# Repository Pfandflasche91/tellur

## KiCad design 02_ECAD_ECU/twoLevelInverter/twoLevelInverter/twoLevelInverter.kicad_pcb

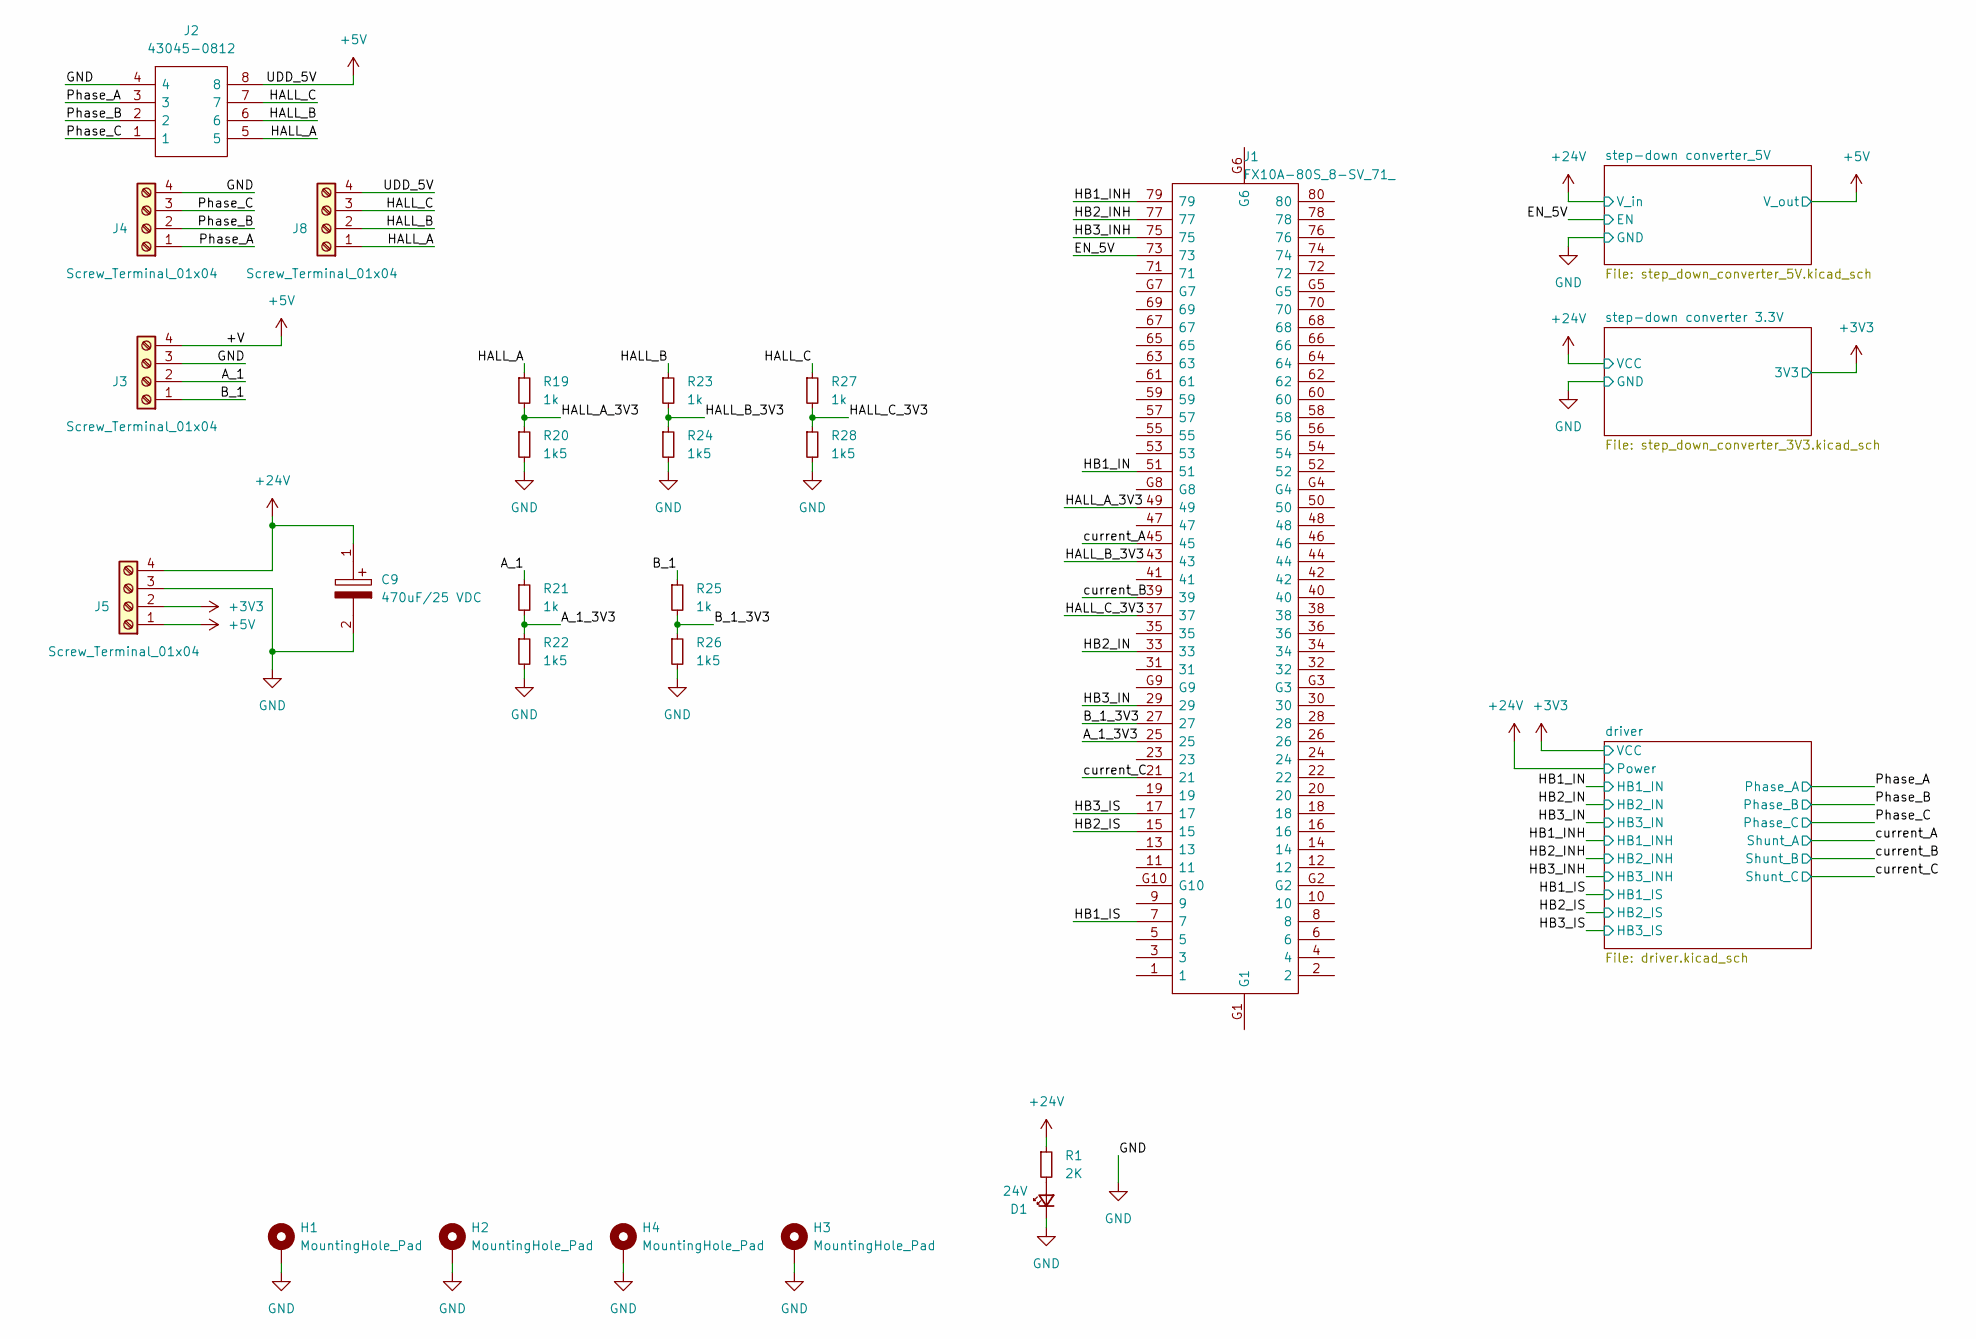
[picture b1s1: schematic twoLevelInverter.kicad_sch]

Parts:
C9: 470uF/25 VDC; CAPAE1030X1050N; Mouser Part Number 710-865080457015
D1: 24V; LED_0805_2012Metric
H1, H2, H3, H4: MountingHole_Pad; MountingHole_5.3mm_M5_Pad_Via
J1: FX10A-80S_8-SV_71_; FX10A80S8SV71; Mouser Part Number 798-FX10A80S8SV71
J2: 43045-0812; 43045-08YY_121314; Mouser Part Number 538-43045-0812
J3, J4, J5, J8: Screw_Terminal_01x04; screwconnector_4_wuerth
R1: 2K; R_1206_3216Metric
R19, R21, R23, R25, R27: 1k; R_1206_3216Metric
R20, R22, R24, R26, R28: 1k5; R_1206_3216Metric

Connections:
+3V3: J5.2; also elsewhere on the board
+5V: J2.8, J3.4, J5.1, J8.4; also elsewhere on the board
+24V: C9.1, J5.4, R1.1; also elsewhere on the board
/A_1: J3.2, R21.1
/A_1_3V3: J1.25, R21.2, R22.1
/B_1: J3.1, R25.1
/B_1_3V3: J1.27, R25.2, R26.1
/EN_5V: J1.73; also elsewhere on the board
/HALL_A: J2.5, J8.1, R19.1
/HALL_A_3V3: J1.49, R19.2, R20.1
/HALL_B: J2.6, J8.2, R23.1
/HALL_B_3V3: J1.43, R23.2, R24.1
/HALL_C: J2.7, J8.3, R27.1
/HALL_C_3V3: J1.37, R27.2, R28.1
/HB1_IN: J1.51; also elsewhere on the board
/HB1_INH: J1.79; also elsewhere on the board
/HB1_IS: J1.7; also elsewhere on the board
/HB2_IN: J1.33; also elsewhere on the board
/HB2_INH: J1.77; also elsewhere on the board
/HB2_IS: J1.15; also elsewhere on the board
/HB3_IN: J1.29; also elsewhere on the board
/HB3_INH: J1.75; also elsewhere on the board
/HB3_IS: J1.17; also elsewhere on the board
/Phase_A: J2.3, J4.1; also elsewhere on the board
/Phase_B: J2.2, J4.2; also elsewhere on the board
/Phase_C: J2.1, J4.3; also elsewhere on the board
/current_A: J1.45; also elsewhere on the board
/current_B: J1.39; also elsewhere on the board
/current_C: J1.21; also elsewhere on the board
GND: C9.2, D1.1 (K), H1.1, H2.1, H3.1, H4.1, J2.4, J3.3, J4.4, J5.3, R20.2, R22.2, R24.2, R26.2, R28.2; also elsewhere on the board
unnamed: D1.2 (A), R1.2

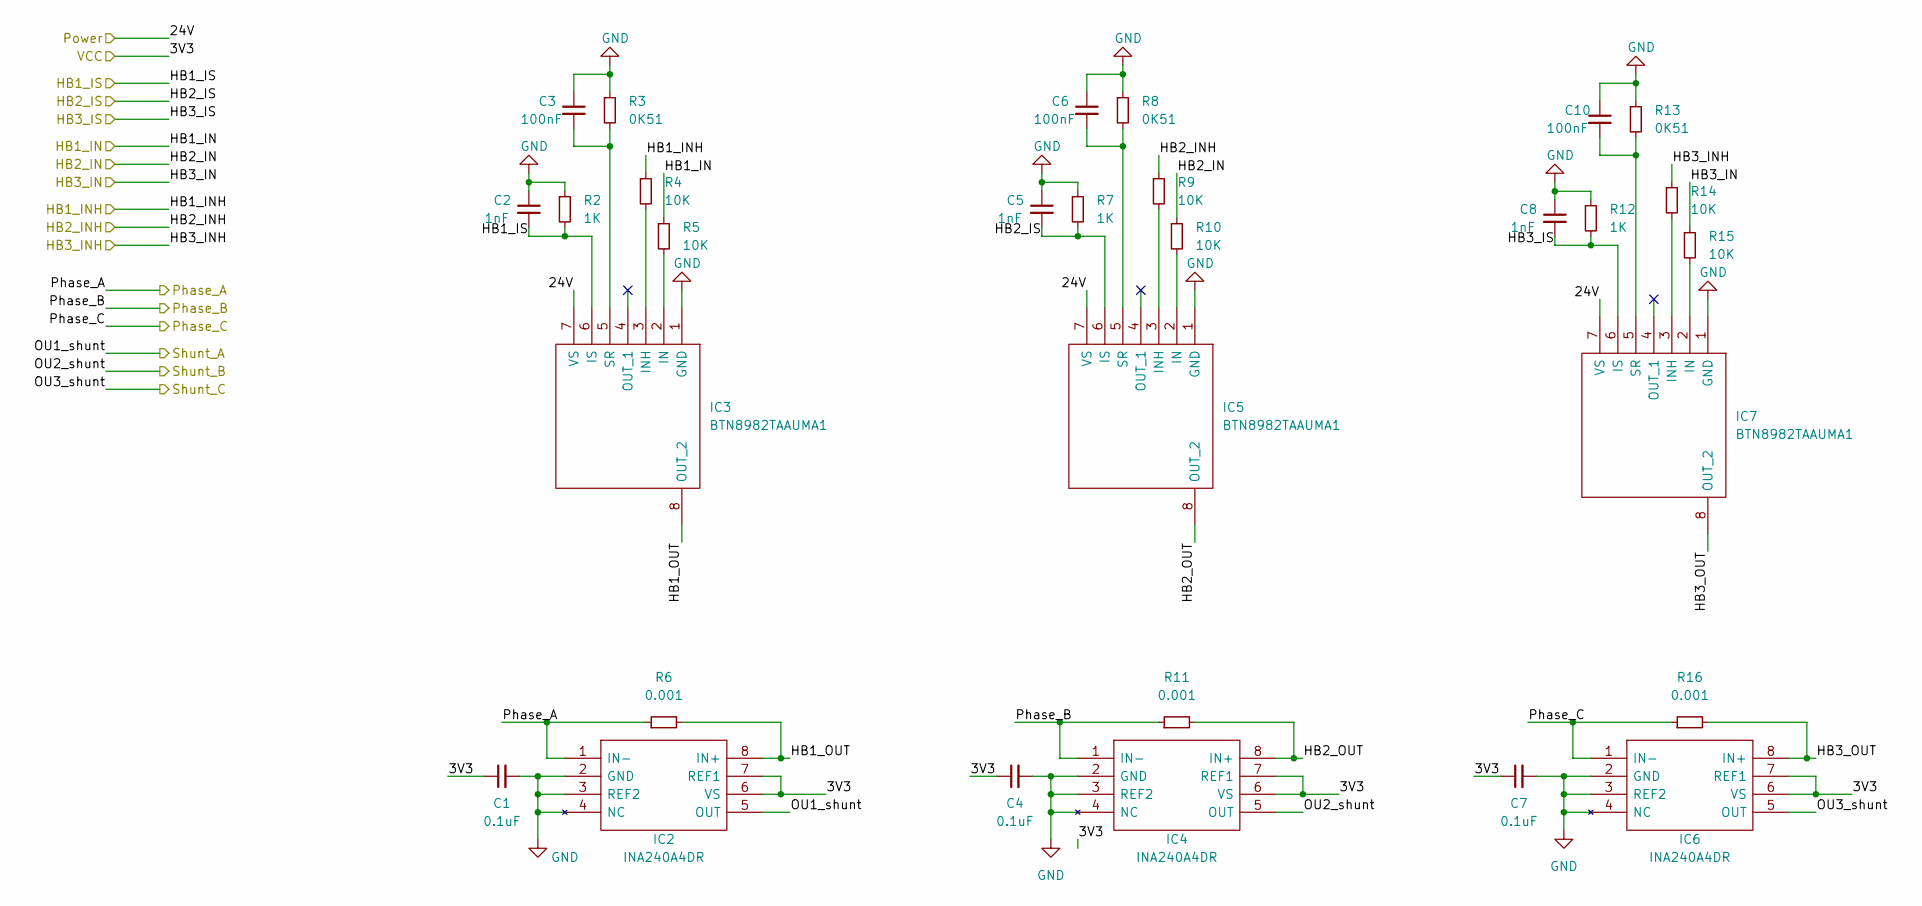
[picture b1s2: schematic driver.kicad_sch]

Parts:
C1, C4, C7: 0.1uF; C_1206_3216Metric
C2, C5, C8: 1nF; C_1206_3216Metric
C3, C6, C10: 100nF; C_1206_3216Metric
IC2, IC4, IC6: INA240A4DR; SOIC127P600X175-8N; Mouser Part Number 595-INA240A4DR
IC3, IC5, IC7: BTN8982TAAUMA1; PG-TO263-7-1; Mouser Part Number 726-BTN8982TAAUMA1
R2, R7, R12: 1K; R_1206_3216Metric
R3, R8, R13: 0K51; R_1206_3216Metric
R4, R5, R9, R10, R14, R15: 10K; R_1206_3216Metric
R6, R11, R16: 0.001; R_1206_3216Metric

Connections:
+3V3: C1.1, C4.1, C7.1, IC2.6 (VS), IC2.7 (REF1), IC4.6 (VS), IC4.7 (REF1), IC6.6 (VS), IC6.7 (REF1); also elsewhere on the board
+24V: IC3.7 (VS), IC5.7 (VS), IC7.7 (VS); also elsewhere on the board
/HB1_IN: R5.1; also elsewhere on the board
/HB1_INH: R4.1; also elsewhere on the board
/HB1_IS: C2.2, IC3.6 (IS), R2.2; also elsewhere on the board
/HB2_IN: R10.1; also elsewhere on the board
/HB2_INH: R9.1; also elsewhere on the board
/HB2_IS: C5.2, IC5.6 (IS), R7.2; also elsewhere on the board
/HB3_IN: R15.1; also elsewhere on the board
/HB3_INH: R14.1; also elsewhere on the board
/HB3_IS: C8.2, IC7.6 (IS), R12.2; also elsewhere on the board
/Phase_A: IC2.1 (IN-), R6.1; also elsewhere on the board
/Phase_B: IC4.1 (IN-), R11.1; also elsewhere on the board
/Phase_C: IC6.1 (IN-), R16.1; also elsewhere on the board
/current_A: IC2.5 (OUT); also elsewhere on the board
/current_B: IC4.5 (OUT); also elsewhere on the board
/current_C: IC6.5 (OUT); also elsewhere on the board
/driver/HB1_OUT: IC2.8 (IN+), IC3.8 (OUT_2), R6.2
/driver/HB2_OUT: IC4.8 (IN+), IC5.8 (OUT_2), R11.2
/driver/HB3_OUT: IC6.8 (IN+), IC7.8 (OUT_2), R16.2
GND: C1.2, C2.1, C3.1, C4.2, C5.1, C6.1, C7.2, C8.1, C10.1, IC2.2 (GND), IC2.3 (REF2), IC2.4 (NC), IC3.1 (GND), IC4.2 (GND), IC4.3 (REF2), IC4.4 (NC), IC5.1 (GND), IC6.2 (GND), IC6.3 (REF2), IC6.4 (NC), IC7.1 (GND), R2.1, R3.1, R7.1, R8.1, R12.1, R13.1; also elsewhere on the board
unnamed: C3.2, IC3.5 (SR), R3.2
unnamed: C6.2, IC5.5 (SR), R8.2
unnamed: C10.2, IC7.5 (SR), R13.2
unnamed: IC3.2 (IN), R5.2
unnamed: IC3.3 (INH), R4.2
unnamed: IC5.2 (IN), R10.2
unnamed: IC5.3 (INH), R9.2
unnamed: IC7.2 (IN), R15.2
unnamed: IC7.3 (INH), R14.2

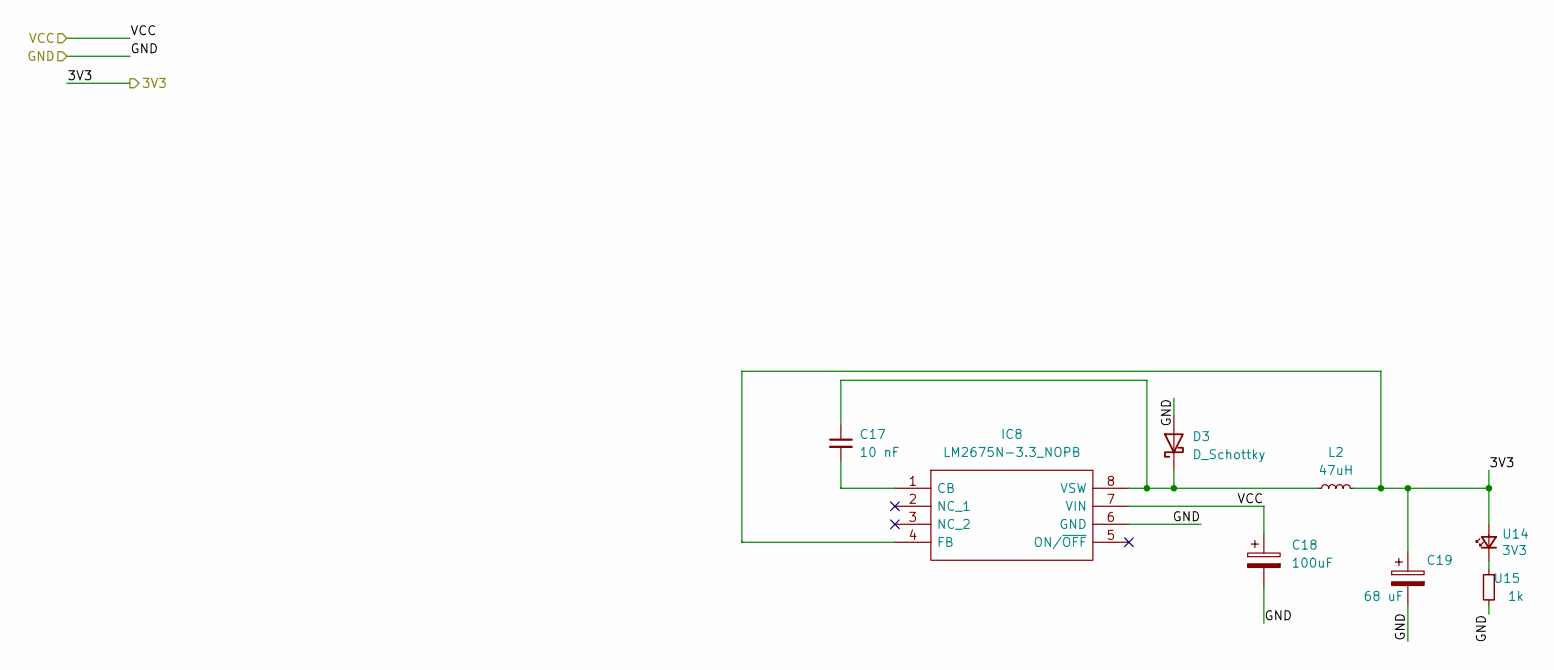
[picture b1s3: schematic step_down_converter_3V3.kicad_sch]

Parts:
C17: 10 nF; C_1206_3216Metric
C18: 100uF; 100uF_wuerth
C19: 68 uF; 68uFcap
D3: D_Schottky; schottydiode50V
IC8: LM2675N-3.3_NOPB; LM2675N; Mouser Part Number 926-LM2675N-33/NOPB
L2: 47uH; C_0805_2012Metric
U14: 3V3; LED_0805_2012Metric; LCSC part # C2286
U15: 1k; R_1206_3216Metric; LCSC part # C4410

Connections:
+3V3: C19.1, IC8.4 (FB), L2.2, U14.2 (A); also elsewhere on the board
+24V: C18.1, IC8.7 (VIN); also elsewhere on the board
GND: C18.2, C19.2, D3.2 (A), IC8.6 (GND), U15.2; also elsewhere on the board
unnamed: C17.1, D3.1 (K), IC8.8 (VSW), L2.1
unnamed: C17.2, IC8.1 (CB)
unnamed: U14.1 (K), U15.1

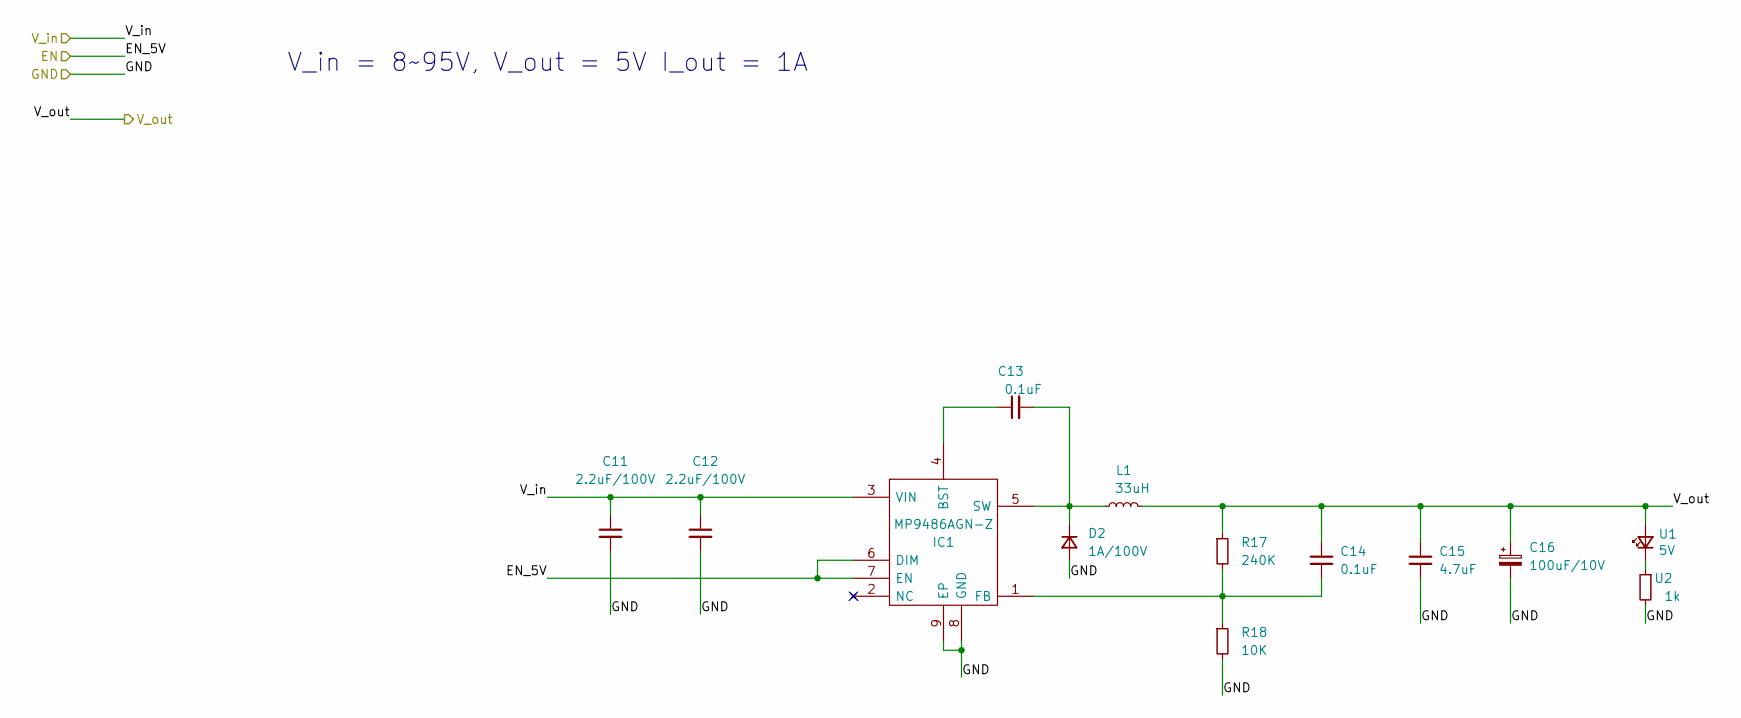
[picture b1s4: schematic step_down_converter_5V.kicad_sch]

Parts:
C11, C12: 2.2uF/100V; C_1206_3216Metric
C13, C14: 0.1uF; C_1206_3216Metric
C15: 4.7uF; C_1206_3216Metric
C16: 100uF/10V; 100uF_wuerth
D2: 1A/100V; D_SOD-323
IC1: MP9486AGN-Z; SOIC127P600X170-9N; Mouser Part Number 946-MP9486AGN-Z
L1: 33uH; 33uH_wuerth_7447706330
R17: 240K; C_1206_3216Metric
R18: 10K; C_1206_3216Metric
U1: 5V; LED_0805_2012Metric; LCSC part # C2286
U2: 1k; R_1206_3216Metric; LCSC part # C4410

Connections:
+5V: C14.1, C15.1, C16.1, L1.2, R17.1, U1.2 (A); also elsewhere on the board
+24V: C11.1, C12.1, IC1.3 (VIN); also elsewhere on the board
/EN_5V: IC1.6 (DIM), IC1.7 (EN); also elsewhere on the board
GND: C11.2, C12.2, C15.2, C16.2, D2.2 (A), IC1.8 (GND), IC1.9 (EP), R18.2, U2.2; also elsewhere on the board
unnamed: C13.1, IC1.4 (BST)
unnamed: C13.2, D2.1 (K), IC1.5 (SW), L1.1
unnamed: C14.2, IC1.1 (FB), R17.2, R18.1
unnamed: U1.1 (K), U2.1

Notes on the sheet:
V_in = 8~95V, V_out = 5V I_out = 1A

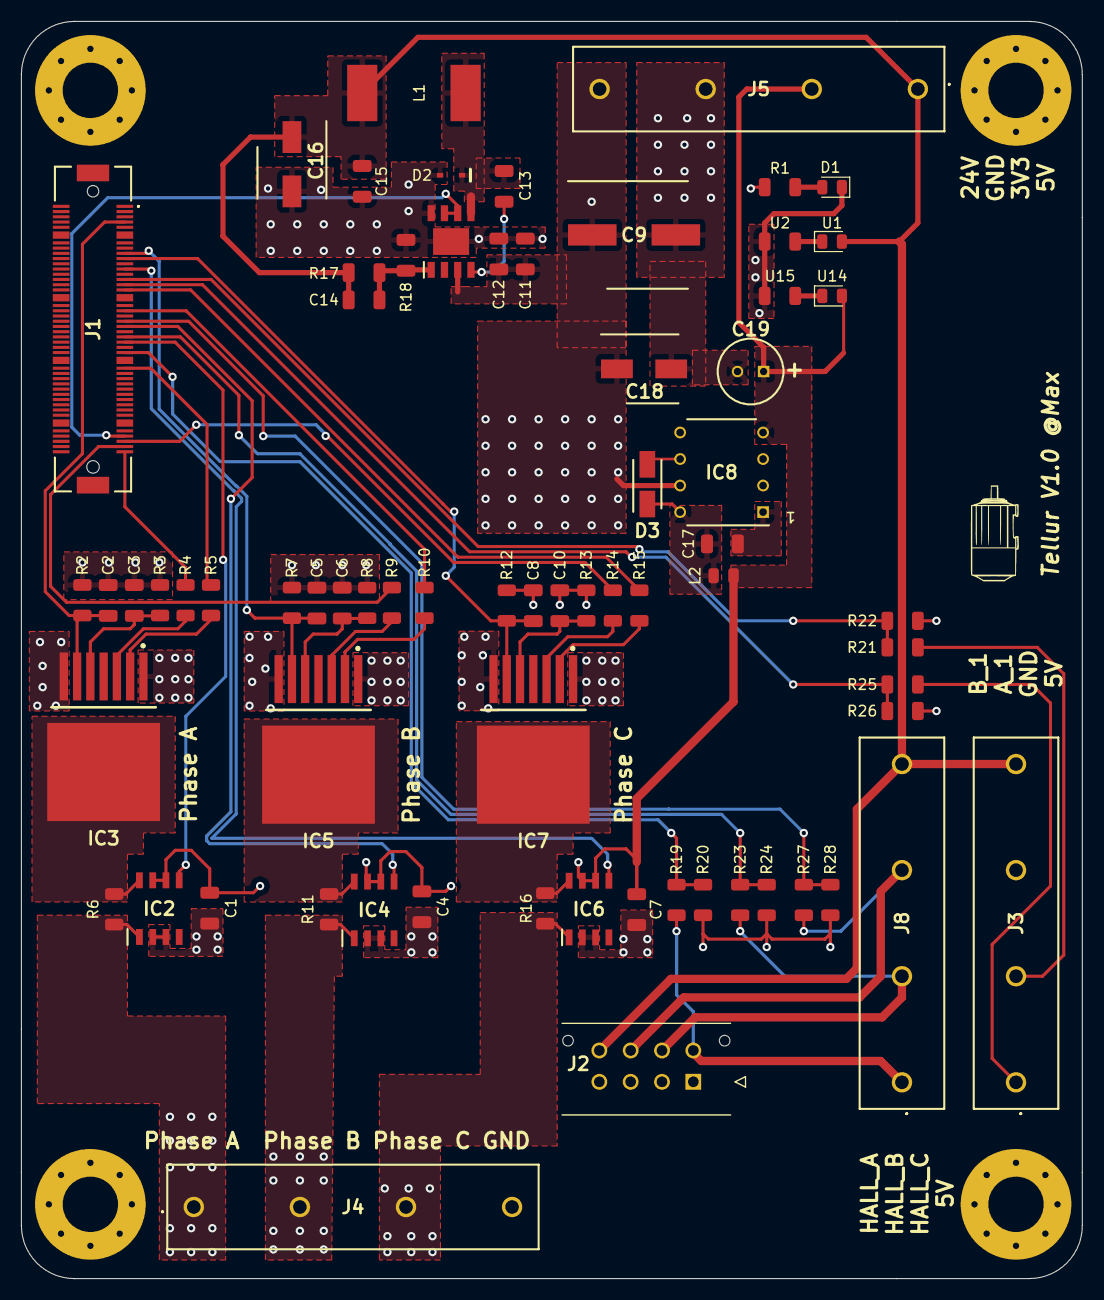
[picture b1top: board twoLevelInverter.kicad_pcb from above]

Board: 4 copper layers, 101.6 x 120.4 mm, 74 parts (0 on the bottom side), 50 nets.

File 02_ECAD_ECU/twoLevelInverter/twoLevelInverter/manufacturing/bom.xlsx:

Comment | Designator | Footprint | JLCPCB Part #（optional）
100nF | C3, C6, C10,C1, C4, C7, C13, C14 | C_1206_3216Metric | C24497
1nF | C2, C5, C8 | C_1206_3216Metric | C9196
2.2uF | C11, C12 | C_1206_3216Metric | C50254
4.7uF | C15 | C_1206_3216Metric | C29823
10nF | C17 | C_1206_3216Metric | C1846
led yellow | D1,U14,U1 | LED_0805 | C2296
2k | R1 | R_1206_3216Metric | C17944
1k | R2, R7, R12,R19, R21, R23, R25, R27,R20, R22, R24, R26, R28,U2, U15 | R_1206_3216Metric | C4410
510 | R3, R8, R13 | R_1206_3216Metric | C2930377
10k | R4, R5, R9, R10, R14, R15,R18 | R_1206_3216Metric | C17902
240k | R17 | R_1206_3216Metric | C294773

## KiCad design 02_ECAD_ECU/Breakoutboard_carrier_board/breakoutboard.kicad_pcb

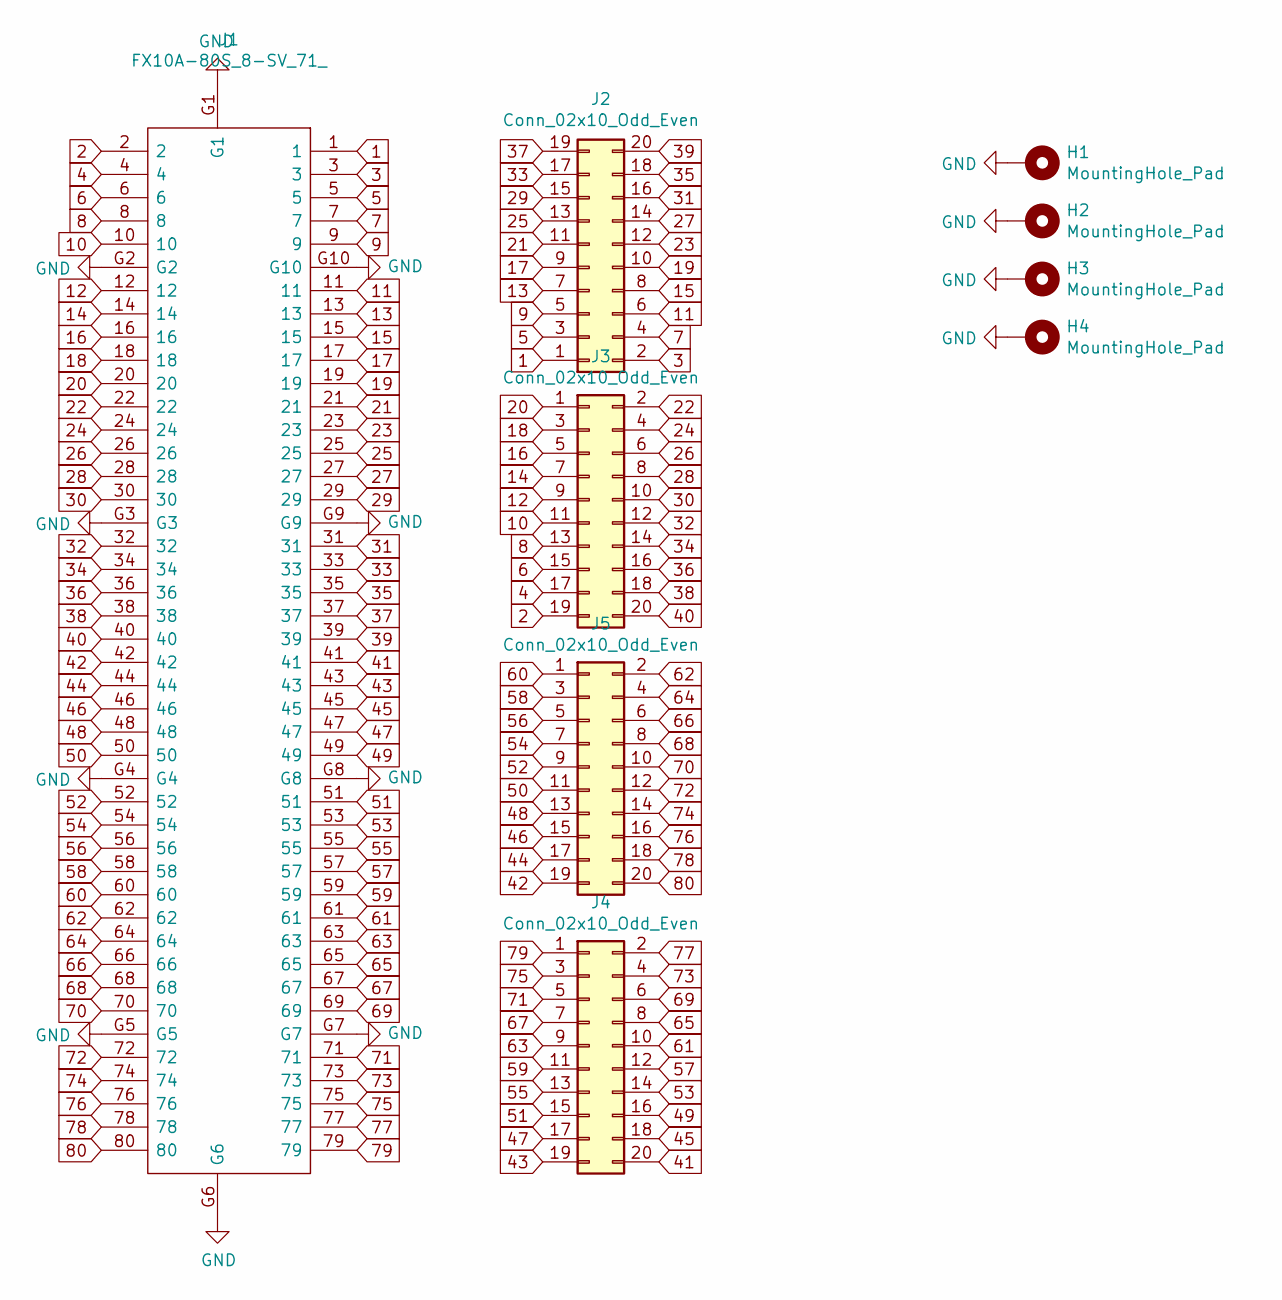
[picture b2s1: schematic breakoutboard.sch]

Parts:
H1, H2, H3, H4: MountingHole_Pad; MountingHole_2.2mm_M2_Pad_Via
J1: FX10A-80S_8-SV_71_; FX10A80S8SV71; Mouser Part Number 798-FX10A80S8SV71
J2, J3, J4, J5: Conn_02x10_Odd_Even; PinHeader_2x10_P2.00mm_Vertical

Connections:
1: J1.1, J2.1
2: J1.2, J3.19
3: J1.3, J2.2
4: J1.4, J3.17
5: J1.5, J2.3
6: J1.6, J3.15
7: J1.7, J2.4
8: J1.8, J3.13
9: J1.9, J2.5
10: J1.10, J3.11
11: J1.11, J2.6
12: J1.12, J3.9
13: J1.13, J2.7
14: J1.14, J3.7
15: J1.15, J2.8
16: J1.16, J3.5
17: J1.17, J2.9
18: J1.18, J3.3
19: J1.19, J2.10
20: J1.20, J3.1
21: J1.21, J2.11
22: J1.22, J3.2
23: J1.23, J2.12
24: J1.24, J3.4
25: J1.25, J2.13
26: J1.26, J3.6
27: J1.27, J2.14
28: J1.28, J3.8
29: J1.29, J2.15
30: J1.30, J3.10
31: J1.31, J2.16
32: J1.32, J3.12
33: J1.33, J2.17
34: J1.34, J3.14
35: J1.35, J2.18
36: J1.36, J3.16
37: J1.37, J2.19
38: J1.38, J3.18
39: J1.39, J2.20
40: J1.40, J3.20
41: J1.41, J4.20
42: J1.42, J5.19
43: J1.43, J4.19
44: J1.44, J5.17
45: J1.45, J4.18
46: J1.46, J5.15
47: J1.47, J4.17
48: J1.48, J5.13
49: J1.49, J4.16
50: J1.50, J5.11
51: J1.51, J4.15
52: J1.52, J5.9
53: J1.53, J4.14
54: J1.54, J5.7
55: J1.55, J4.13
56: J1.56, J5.5
57: J1.57, J4.12
58: J1.58, J5.3
59: J1.59, J4.11
60: J1.60, J5.1
61: J1.61, J4.10
62: J1.62, J5.2
63: J1.63, J4.9
64: J1.64, J5.4
65: J1.65, J4.8
66: J1.66, J5.6
67: J1.67, J4.7
68: J1.68, J5.8
69: J1.69, J4.6
70: J1.70, J5.10
71: J1.71, J4.5
72: J1.72, J5.12
73: J1.73, J4.4
74: J1.74, J5.14
75: J1.75, J4.3
76: J1.76, J5.16
77: J1.77, J4.2
78: J1.78, J5.18
79: J1.79, J4.1
80: J1.80, J5.20
GND: H1.1, H2.1, H3.1, H4.1, J1.G1, J1.G2, J1.G3, J1.G4, J1.G5, J1.G6, J1.G7, J1.G8, J1.G9, J1.G10

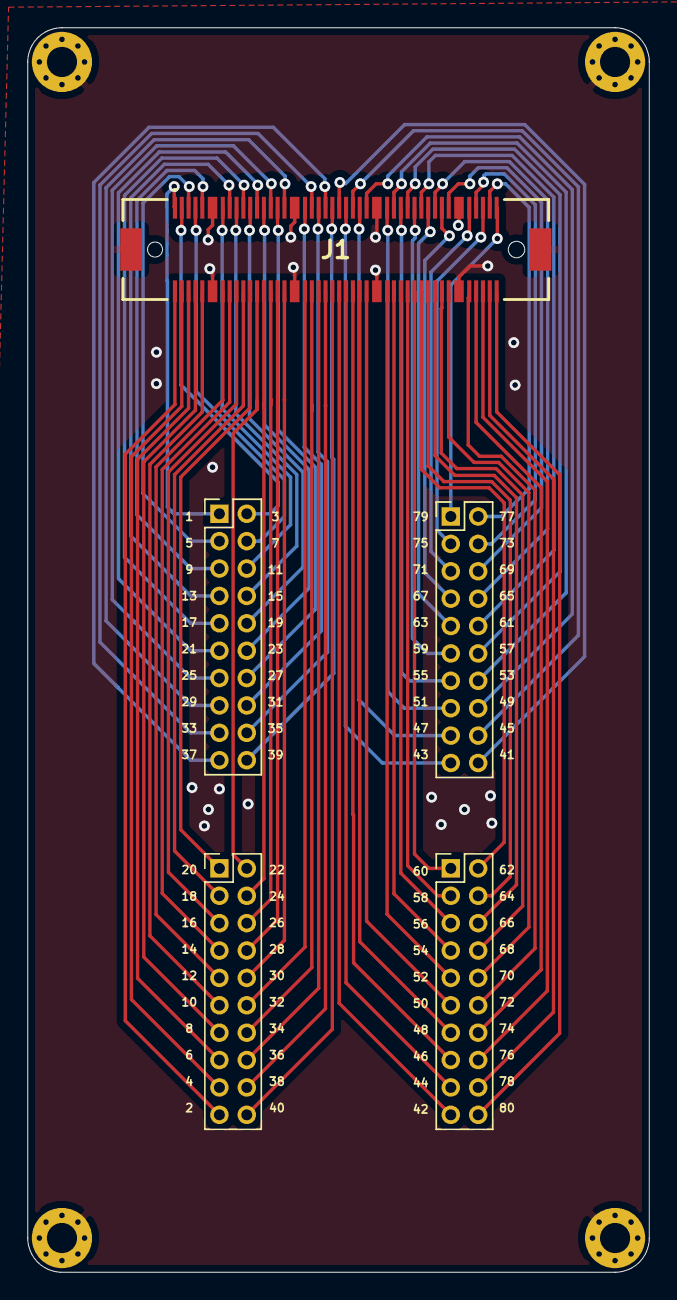
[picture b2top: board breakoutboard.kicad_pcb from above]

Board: 2 copper layers, 45.4 x 90.9 mm, 9 parts (0 on the bottom side), 81 nets.

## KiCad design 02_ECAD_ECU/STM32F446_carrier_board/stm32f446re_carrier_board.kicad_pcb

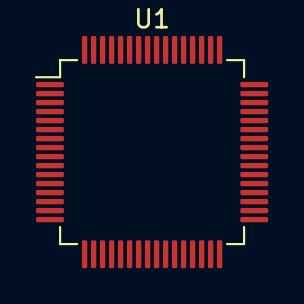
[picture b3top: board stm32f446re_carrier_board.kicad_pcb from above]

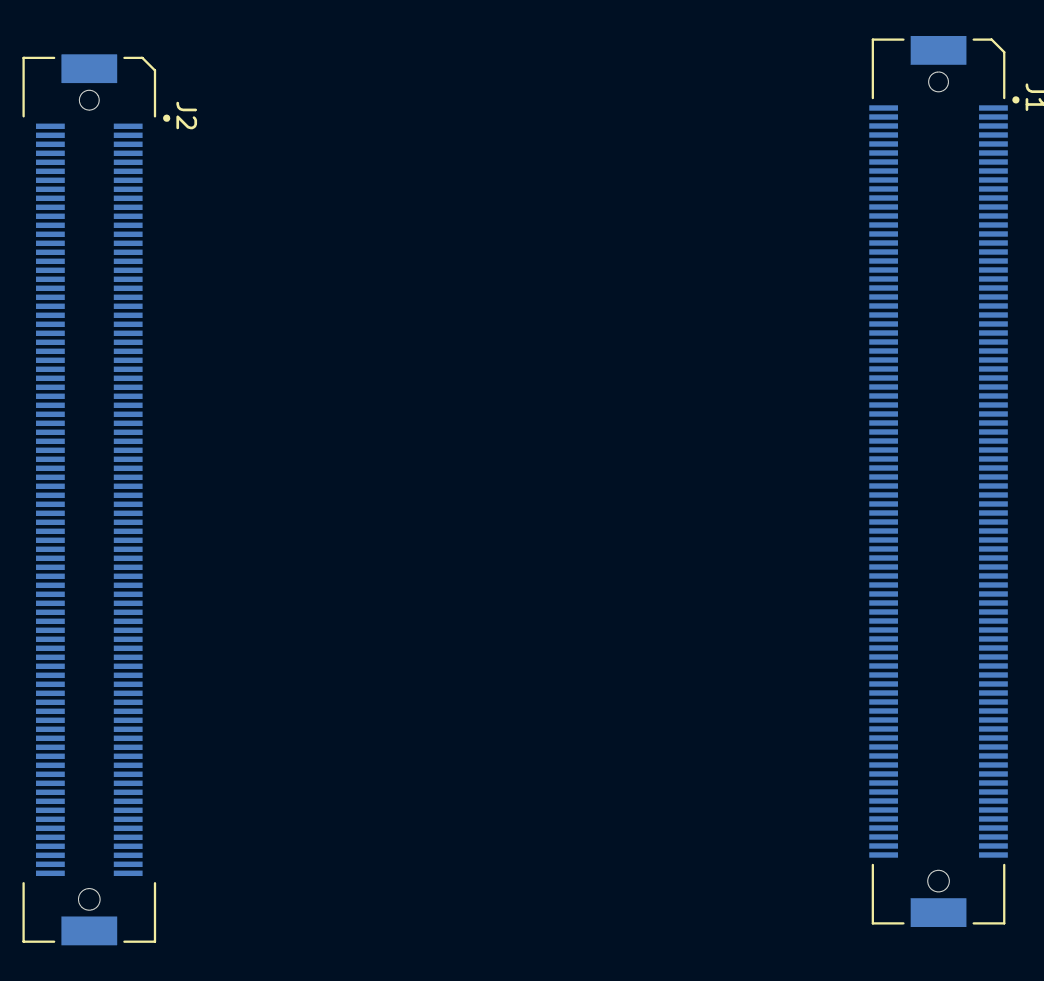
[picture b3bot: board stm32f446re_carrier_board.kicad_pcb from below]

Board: 2 copper layers, 3 parts (2 on the bottom side), 2 nets, no tracks yet.

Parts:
J1: FX10A-168S-SV; HRS_FX10A-168S-SV
J2: FX10A-168P-SV_(71); HRS_FX10A-168P-SV
U1: STM32F446RETx; LQFP-64_10x10mm_P0.5mm

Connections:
unnamed: J1.S1, J1.S2
unnamed: J2.S1, J2.S2

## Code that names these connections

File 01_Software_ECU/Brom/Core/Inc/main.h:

/* USER CODE BEGIN Header */
/**
  ******************************************************************************
  * @file           : main.h
  * @brief          : Header for main.c file.
  *                   This file contains the common defines of the application.
  ******************************************************************************
  * @attention
  *
  * <h2><center>&copy; Copyright (c) 2021 STMicroelectronics.
  * All rights reserved.</center></h2>
  *
  * This software component is licensed by ST under BSD 3-Clause license,
  * the "License"; You may not use this file except in compliance with the
  * License. You may obtain a copy of the License at:
  *                        opensource.org/licenses/BSD-3-Clause
  *
  ******************************************************************************
  */
/* USER CODE END Header */

/* Define to prevent recursive inclusion -------------------------------------*/
#ifndef __MAIN_H
#define __MAIN_H

#ifdef __cplusplus
extern "C" {
#endif

/* Includes ------------------------------------------------------------------*/
#include "stm32f4xx_hal.h"

/* Private includes ----------------------------------------------------------*/
/* USER CODE BEGIN Includes */

/* USER CODE END Includes */

/* Exported types ------------------------------------------------------------*/
/* USER CODE BEGIN ET */

/* USER CODE END ET */

/* Exported constants --------------------------------------------------------*/
/* USER CODE BEGIN EC */

/* USER CODE END EC */

/* Exported macro ------------------------------------------------------------*/
/* USER CODE BEGIN EM */

/* USER CODE END EM */

void HAL_TIM_MspPostInit(TIM_HandleTypeDef *htim);

/* Exported functions prototypes ---------------------------------------------*/
void Error_Handler(void);

/* USER CODE BEGIN EFP */
void control(void);

/* USER CODE END EFP */

/* Private defines -----------------------------------------------------------*/
#define LED_Pin GPIO_PIN_2
#define LED_GPIO_Port GPIOA
#define EN_5V_Pin GPIO_PIN_9
#define EN_5V_GPIO_Port GPIOC
#define HB3_INH_Pin GPIO_PIN_8
#define HB3_INH_GPIO_Port GPIOA
#define HB2_INH_Pin GPIO_PIN_9
#define HB2_INH_GPIO_Port GPIOA
#define HB1_INH_Pin GPIO_PIN_10
#define HB1_INH_GPIO_Port GPIOA

/* USER CODE BEGIN Private defines */


/* USER CODE END Private defines */

#ifdef __cplusplus
}
#endif

#endif /* __MAIN_H */

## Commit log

2021-09-07 added submodule kicad_lib for KiCAD parts
2021-09-07 added photon project
2021-09-07 CMSIS LIB integration
2021-09-07 function by my own
2021-09-07 added gitignore stuff
2021-09-07 cmsis_mcal working
2021-09-07 changed git ignore
2021-09-07 created libs
2021-09-07 added gitignore
2021-09-07 edit: comments
2021-09-07 edit: gitignore
2021-09-07 edit : comments
2021-09-07 edit debug files
2021-09-07 rectangle function test edit
2021-09-07 edit gitignore
2021-09-07 working
2021-09-08 file: added KiCAD project for carrier board
2021-09-16 added lib to project
2021-09-16 edit
2021-09-16 added submodule catalyst ( python gui)
2021-09-16 deletet submodule
2021-09-16 added submodules in the right place now
2021-09-16 added connectors to ecad project
2021-09-19 carrierboard stm32f446 finished v0.1
2021-09-19 Removed submodule 02_ECAD_ECU/kicad_lib
2021-09-19 created kicad breakoutboard project
2021-09-20 finished breakoutbox and orderd
2021-12-28 added timer struct and driver files
    first steps to running timer. Added typdef in stm32f4.. . added driver files
2021-12-28 cubmx project implementation
    added LED status & UART COM Driver
2022-10-13 saving
2022-11-24 added USB functions
2022-11-24 init Kicad project
2023-01-06 V0.0 missing layouting and some components
2023-01-16 adding PID control simulation
2023-01-22 added RCFilter & tested 20khz timer
2023-01-25 working i hope
2023-02-06 added encoder first steps
2023-02-19 uart testing
2023-03-20 mapped all signals so fare
2023-03-20 encoder, pwm, hall signals mapped
2023-03-20 added HBx_IS and HBx_INH and EN_step_down
2023-03-23 V1.0 not reviewed
2023-03-24 orderd, added gerber files
2023-04-28 clean up , usb com basic working
2023-05-21 write and read over usb
2023-09-18 test setup
2023-10-07 first implementation of communication , working but not perfect
2023-12-09 communication working, split in dedicated file
2023-12-09 "merged" schematic for inverter to folder
2023-12-13 block commutation working, basic scheduler
